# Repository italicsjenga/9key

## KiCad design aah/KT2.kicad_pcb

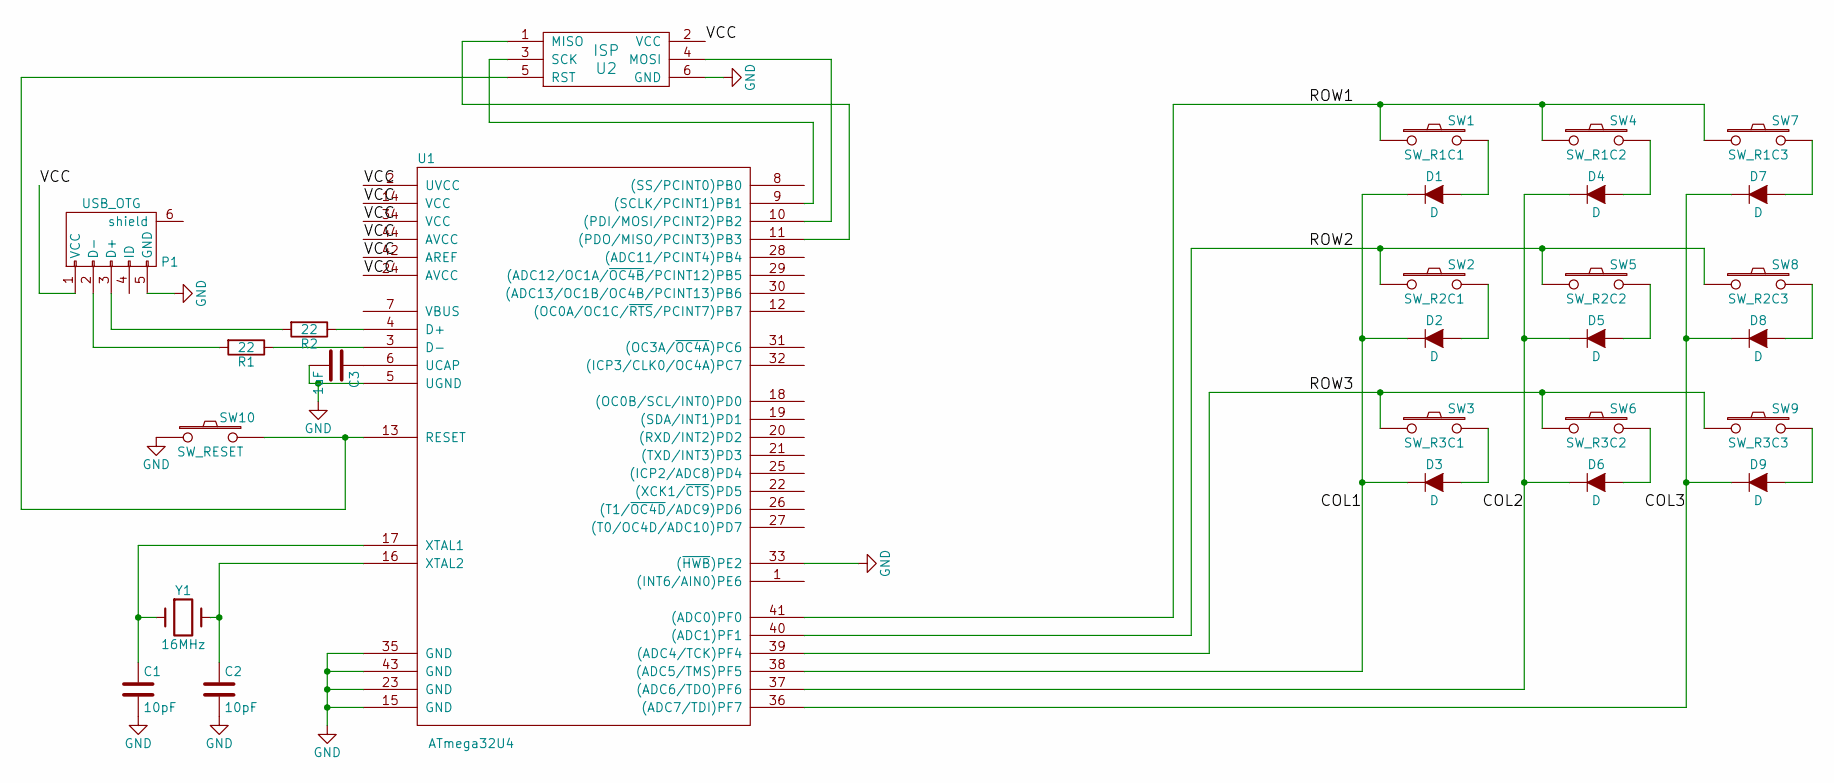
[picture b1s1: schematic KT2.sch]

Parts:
C1, C2: 10pF; C_0603_HandSoldering
C3: 1uF; C_0603_HandSoldering
D1, D2, D3, D4, D5, D6, D7, D8, D9: D; Diode_DO-35_SOD27_Horizontal_RM10
P1: USB_OTG; USB_Mini-B
R1, R2: 22; R_0603_HandSoldering
SW1: SW_R1C1; CHERRY_PCB_100H
SW2: SW_R2C1; CHERRY_PCB_100H
SW3: SW_R3C1; CHERRY_PCB_100H
SW4: SW_R1C2; CHERRY_PCB_100H
SW5: SW_R2C2; CHERRY_PCB_100H
SW6: SW_R3C2; CHERRY_PCB_100H
SW7: SW_R1C3; CHERRY_PCB_100H
SW8: SW_R2C3; CHERRY_PCB_100H
SW9: SW_R3C3; CHERRY_PCB_100H
SW10: SW_RESET; SW_SPST_FSMSM
U1: ATmega32U4; TQFP-44_10x10mm_Pitch0.8mm
U2: ISP; Pin_Header_Straight_2x03
Y1: 16MHz; HC49SM

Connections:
/COL1: D1.1 (K), D2.1 (K), D3.1 (K), U1.38 ((ADC5/TMS)PF5)
/COL2: D4.1 (K), D5.1 (K), D6.1 (K), U1.37 ((ADC6/TDO)PF6)
/COL3: D7.1 (K), D8.1 (K), D9.1 (K), U1.36 ((ADC7/TDI)PF7)
/ROW1: SW1.1, SW4.1, SW7.1, U1.41 ((ADC0)PF0)
/ROW2: SW2.1, SW5.1, SW8.1, U1.40 ((ADC1)PF1)
/ROW3: SW3.1, SW6.1, SW9.1, U1.39 ((ADC4/TCK)PF4)
/VCC: P1.1 (VCC), U1.2 (UVCC), U1.14 (VCC), U1.24 (AVCC), U1.34 (VCC), U1.42 (AREF), U1.44 (AVCC), U2.2 (VCC)
GND: C1.2, C2.2, C3.2, P1.5 (GND), SW10.1, U1.5 (UGND), U1.15 (GND), U1.23 (GND), U1.33 ((~HWB~)PE2), U1.35 (GND), U1.43 (GND), U2.6 (GND)
unnamed: C1.1, U1.17 (XTAL1), Y1.1
unnamed: C2.1, U1.16 (XTAL2), Y1.2
unnamed: C3.1, U1.6 (UCAP)
unnamed: D1.2 (A), SW1.2
unnamed: D2.2 (A), SW2.2
unnamed: D3.2 (A), SW3.2
unnamed: D4.2 (A), SW4.2
unnamed: D5.2 (A), SW5.2
unnamed: D6.2 (A), SW6.2
unnamed: D7.2 (A), SW7.2
unnamed: D8.2 (A), SW8.2
unnamed: D9.2 (A), SW9.2
unnamed: P1.2 (D-), R1.2
unnamed: P1.3 (D+), R2.2
unnamed: R1.1, U1.3 (D-)
unnamed: R2.1, U1.4 (D+)
unnamed: SW10.2, U1.13 (RESET), U2.5 (RST)
unnamed: U1.9 ((SCLK/PCINT1)PB1), U2.3 (SCK)
unnamed: U1.10 ((PDI/MOSI/PCINT2)PB2), U2.4 (MOSI)
unnamed: U1.11 ((PDO/MISO/PCINT3)PB3), U2.1 (MISO)

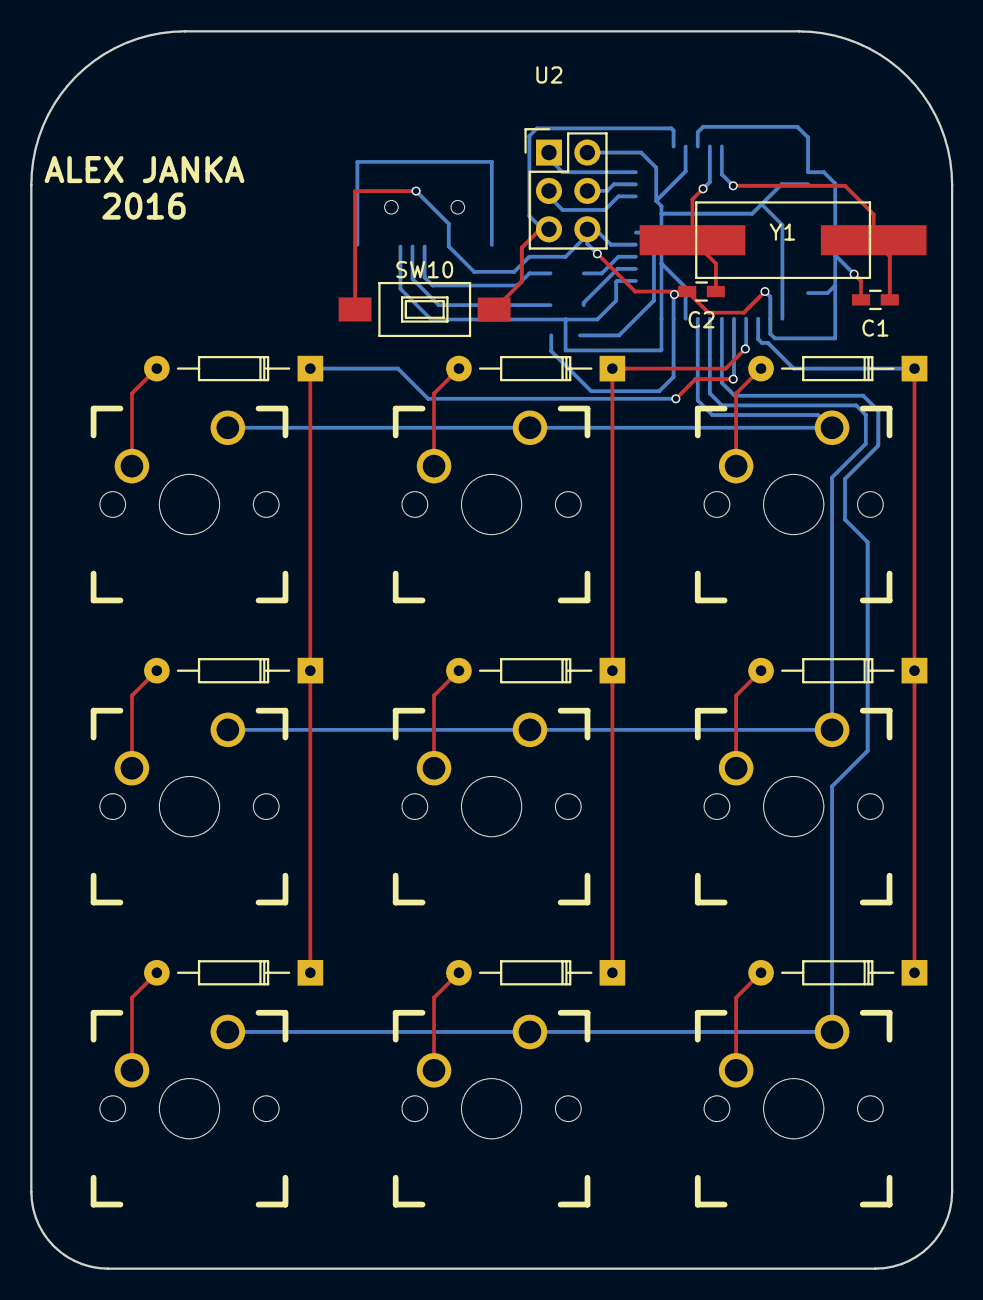
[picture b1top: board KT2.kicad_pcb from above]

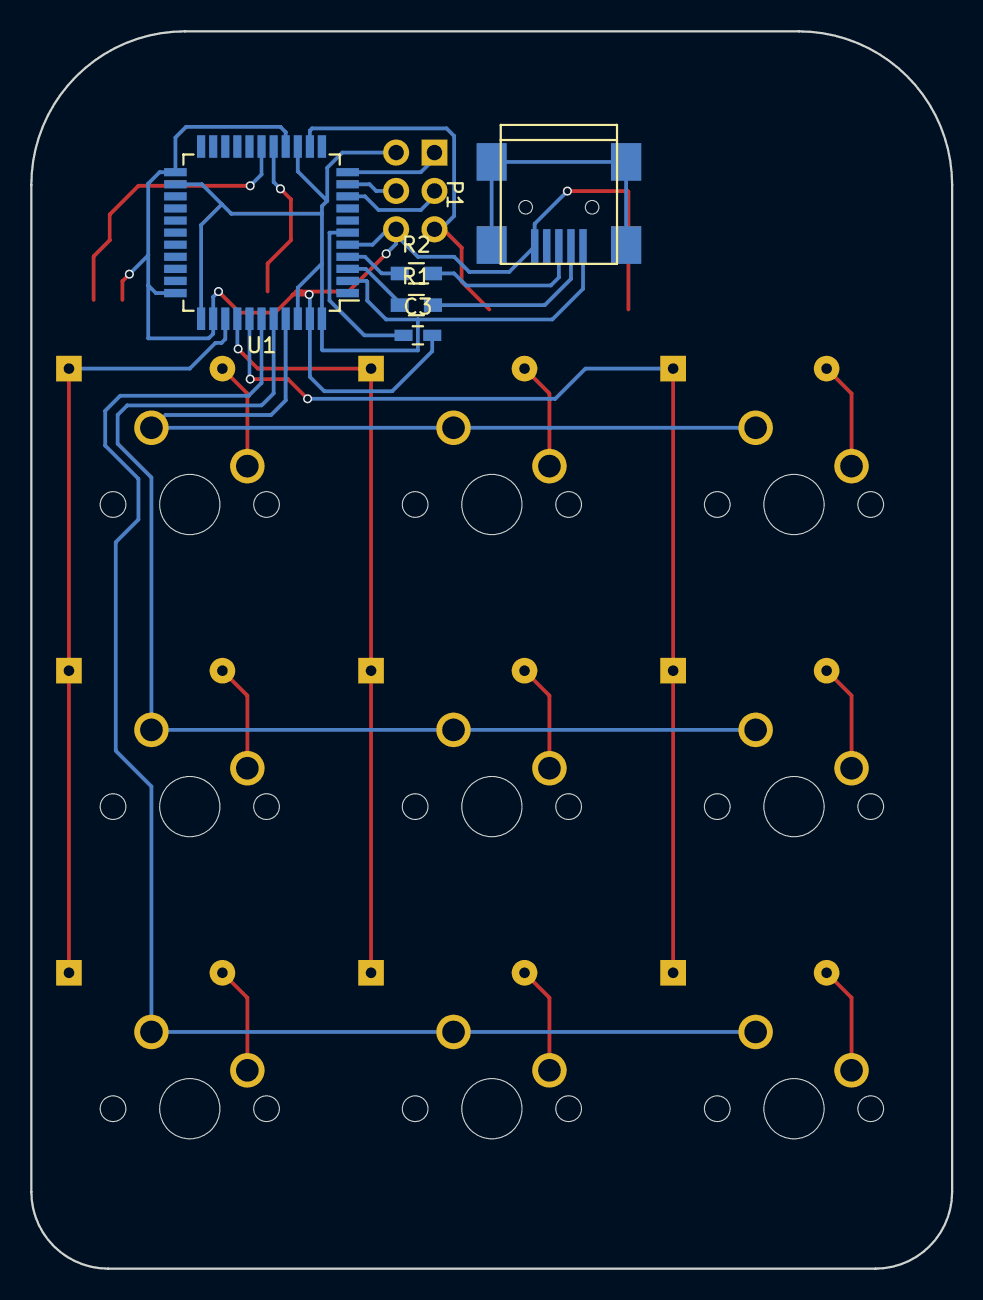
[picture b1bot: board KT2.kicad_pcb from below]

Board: 2 copper layers, 61.0 x 81.9 mm, 28 parts (5 on the bottom side), 28 nets.

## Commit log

2016-06-19 Firsrt commti
